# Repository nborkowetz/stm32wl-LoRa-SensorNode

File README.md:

# STM32WL LoRaWAN Prototyping Platform
## Modular Sensor Node for Industrial IoT & Water Quality Monitoring

## 📌 Project Overview
This repository contains the hardware design for a high-performance, ultra-low-power LoRaWAN node based on the **STM32WL55CCU6** SoC. 

This platform serves as an **architectural evaluation board**. It is designed to validate power management strategies, RF performance, and modular sensor interfacing before final product miniaturization.

## 🛠 Technical Specifications

### Core System
* **MCU:** STM32WL55CCU6 (Dual-core ARM Cortex-M4/M0+).
* **Connectivity:** Sub-GHz radio supporting LoRa, (G)FSK, (G)MSK, and BPSK.
* **RF Path:** Optimized 868MHz output with an integrated **BGS12WN6** RF switch and pi-filter matching network.

### Power Management (Ultra-Low Power Focus)
The hardware implements a sophisticated power tree for extreme battery longevity:
* **TPS63900 Buck-Boost:** High-efficiency converter with ultra-low quiescent current, providing a stable 3.3V output across the entire battery discharge curve.
* **LiFePO4 Charging:** Integrated **BQ25071** linear charger, specifically optimized for the safety and cycle-life requirements of LiFePO4 chemistry.
* **Power Gating:** Dedicated load switches to fully disconnect sensor peripherals during deep-sleep cycles, minimizing leakage current.

### PCB Design & Signal Integrity
* **Layer Stack:** 4-layer design (Signal-GND-PWR-Signal) utilizing the **JLC04161H** stackup.
* **Impedance Control:** * **50Ω Single-Ended:** Precision routing for the RF signal path to the antenna.
  * **90Ω Differential:** Calculated for USB data integrity.
* **Manufacturing Ready:** The layout has successfully passed **DFM (Design for Manufacturing)** suites for industrial production standards.

## 🧪 Modular Sensing Interface
To act as a versatile testbed, the board includes:
* Multi-protocol headers (I2C, SPI, UART).
* Analog conditioning circuitry for environmental probes.
* ESD protection on all external sensor interface lines.

## 📂 Project Status
* **Hardware:** Design finalized and DFM-validated. Ready for prototyping.
* **Firmware:** Under active development. Implementing low-power routines and LoRaWAN stack integration using STM32CubeWL HAL.

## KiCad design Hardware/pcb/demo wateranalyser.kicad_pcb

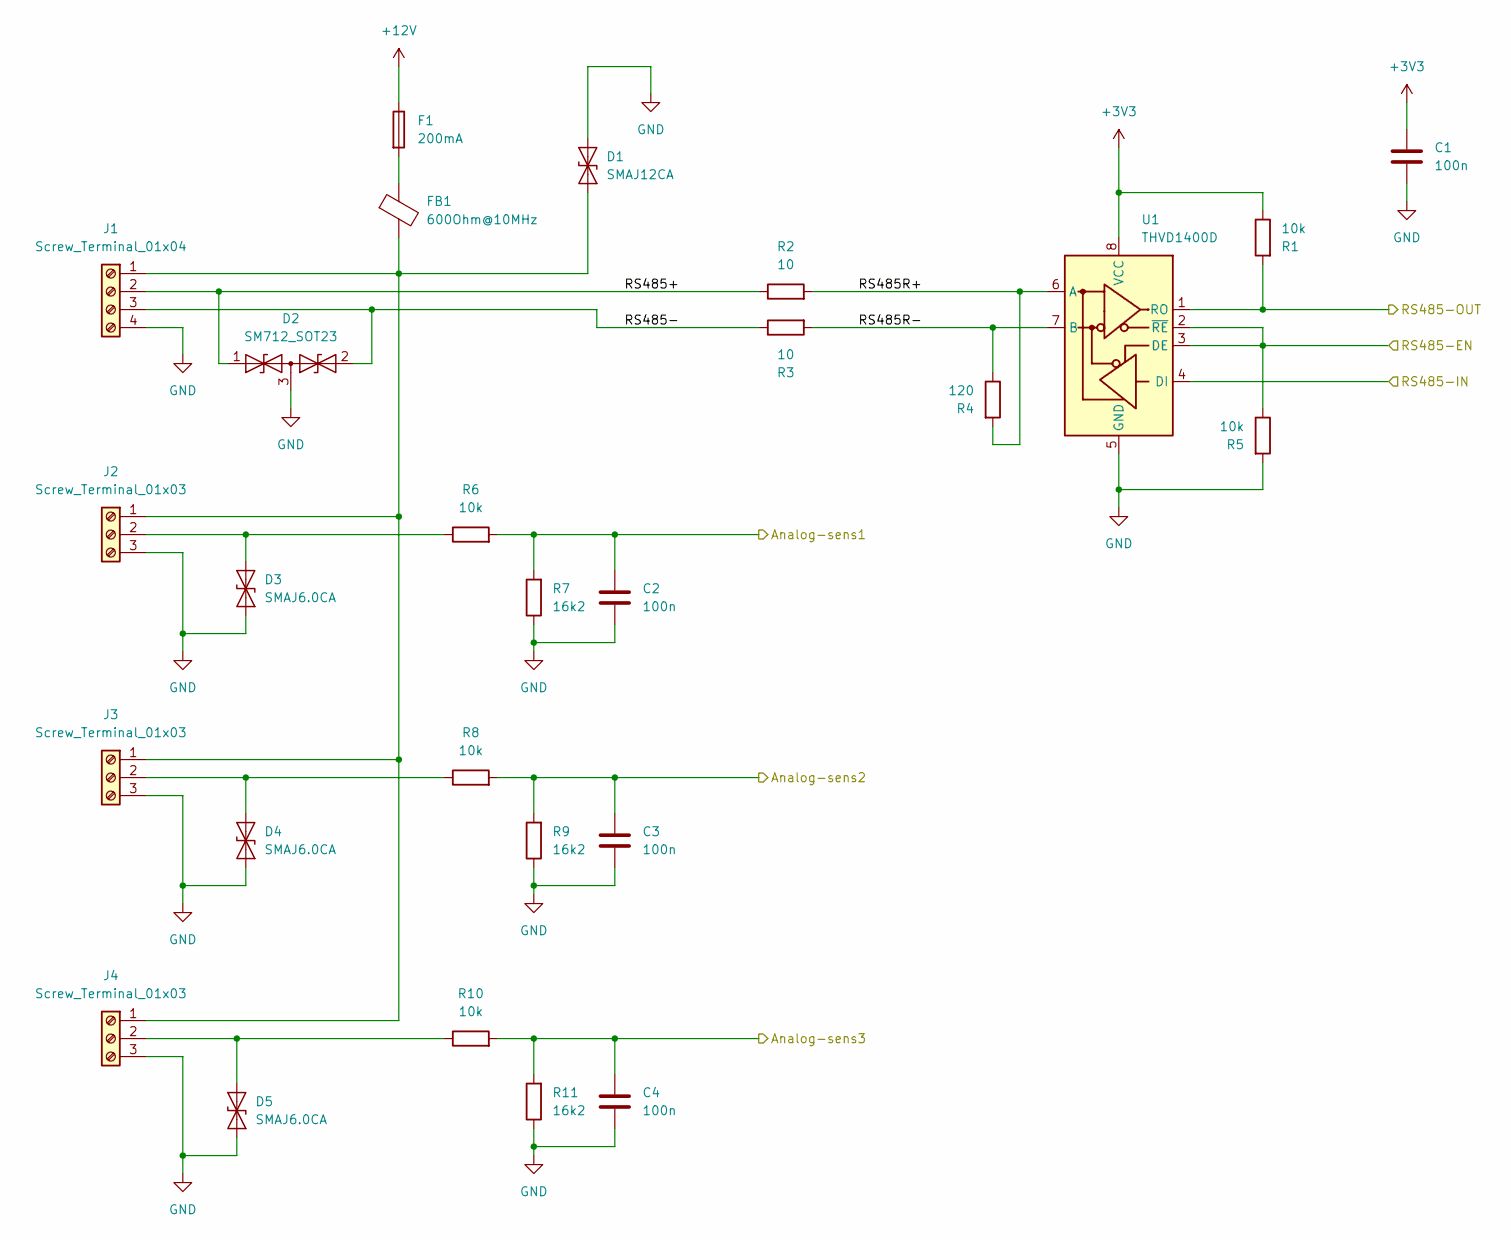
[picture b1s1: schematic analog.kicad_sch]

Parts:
C1, C2, C3, C4: 100n; C_0603_1608Metric
D1: SMAJ12CA; D_SMA
D2: SM712_SOT23; SOT-23
D3, D4, D5: SMAJ6.0CA; D_SMA
F1: 200mA; Fuse_0805_2012Metric
FB1: 600Ohm@10MHz; L_0603_1608Metric
J1: Screw_Terminal_01x04; TerminalBlock_Phoenix_MKDS-1,5-4-5.08_1x04_P5.08mm_Horizont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
J2, J3, J4: Screw_Terminal_01x03; TerminalBlock_Phoenix_MKDS-1,5-3-5.08_1x03_P5.08mm_Horizont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
R1, R5, R6, R8, R10: 10k; R_0603_1608Metric
R2, R3: 10; R_0603_1608Metric
R4: 120; R_0603_1608Metric
R7, R9, R11: 16k2; R_0603_1608Metric
U1: THVD1400D; SOIC-8_3.9x4.9mm_P1.27mm

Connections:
+3V3: C1.1, R1.1, U1.8 (VCC); also elsewhere on the board
+12V: F1.1; also elsewhere on the board
/MCU/ADC-CH2: C2.1, R6.2, R7.2; also elsewhere on the board
/MCU/ADC-CH3: C3.1, R8.2, R9.2; also elsewhere on the board
/MCU/ADC-CH4: C4.1, R10.2, R11.2; also elsewhere on the board
/MCU/RS485-EN: R5.1, U1.2 (~RE), U1.3 (DE); also elsewhere on the board
/MCU/UART-RX: R1.2, U1.1 (RO); also elsewhere on the board
/MCU/UART-TX: U1.4 (DI); also elsewhere on the board
/analog/RS485+: D2.1 (A1), J1.2, R2.1
/analog/RS485-: D2.2 (A2), J1.3, R3.1
/analog/RS485R+: R2.2, R4.2, U1.6 (A)
/analog/RS485R-: R3.2, R4.1, U1.7 (B)
unnamed: D1.1 (A1), FB1.2, J1.1, J2.1, J3.1, J4.1
unnamed: D3.2 (A2), J2.2, R6.1
unnamed: D4.2 (A2), J3.2, R8.1
unnamed: D5.2 (A2), J4.2, R10.1
unnamed: F1.2, FB1.1

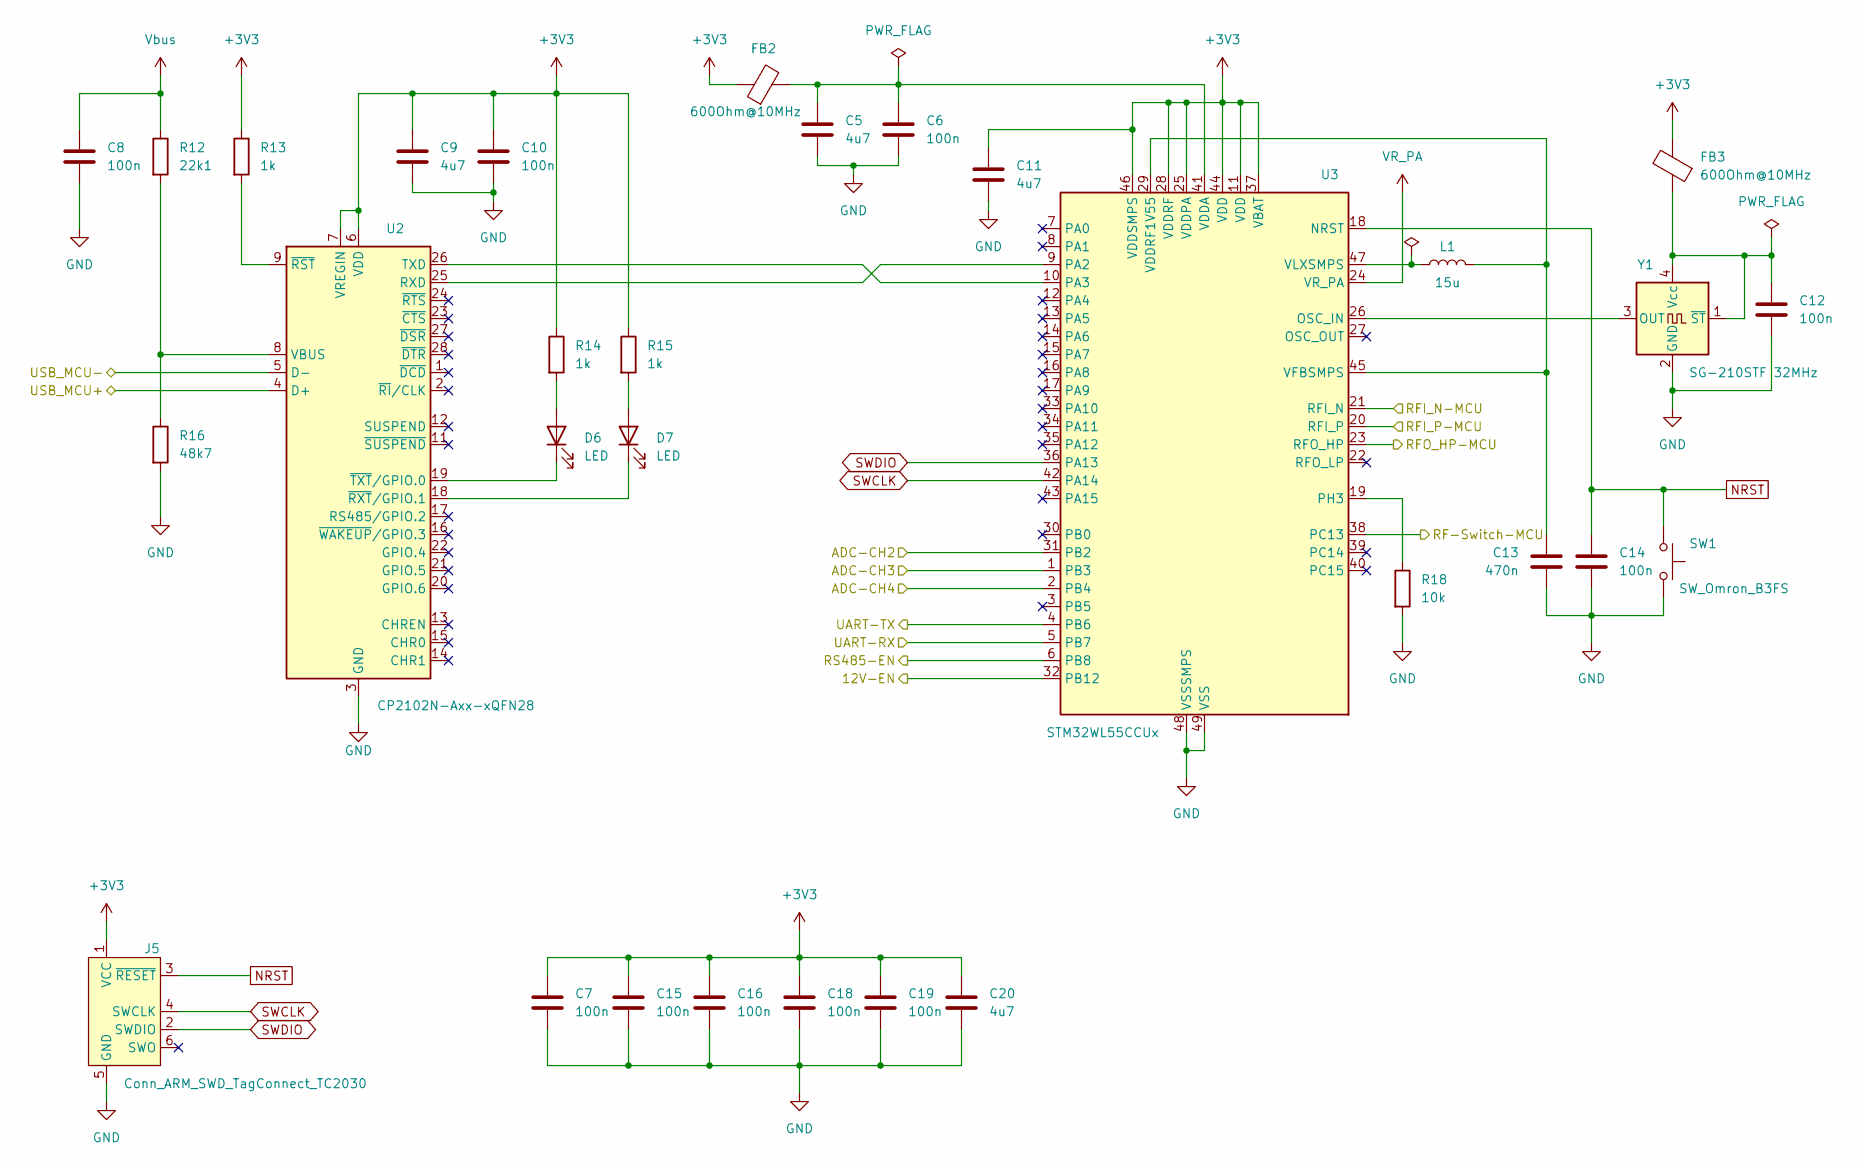
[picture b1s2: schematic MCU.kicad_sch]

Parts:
C5, C9, C11, C20: 4u7; C_0603_1608Metric
C6, C7, C8, C10, C12, C14, C15, C16, C18, C19: 100n; C_0603_1608Metric
C13: 470n; C_0603_1608Metric
D6, D7: LED; LED_0603_1608Metric
FB2, FB3: 600Ohm@10MHz; L_0603_1608Metric
J5: Conn_ARM_SWD_TagConnect_TC2030; Tag-Connect_TC2030-IDC-NL_2x03_P1.27mm_Vertical
L1: 15u; L_0805_2012Metric
R12: 22k1; R_0603_1608Metric
R13, R14, R15: 1k; R_0603_1608Metric
R16: 48k7; R_0603_1608Metric
R18: 10k; R_0603_1608Metric
SW1: SW_Omron_B3FS; SW_SPST_Omron_B3FS-100xP
U2: CP2102N-Axx-xQFN28; QFN-28-1EP_5x5mm_P0.5mm_EP3.35x3.35mm
U3: STM32WL55CCUx; QFN-48-1EP_7x7mm_P0.5mm_EP5.6x5.6mm
Y1: SG-210STF 32MHz; Oscillator_SMD_SeikoEpson_SG210-4Pin_2.5x2.0mm

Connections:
+3V3: C7.1, C9.1, C10.1, C11.1, C15.1, C16.1, C18.1, C19.1, C20.1, FB2.1, FB3.2, J5.1 (VCC), R13.1, R14.1, R15.1, U2.6 (VDD), U2.7 (VREGIN), U3.11 (VDD), U3.25 (VDDPA), U3.28 (VDDRF), U3.37 (VBAT), U3.44 (VDD), U3.46 (VDDSMPS); also elsewhere on the board
/LoRa RF/RF-Switch: U3.38 (PC13); also elsewhere on the board
/LoRa RF/RFI_N: U3.21 (RFI_N); also elsewhere on the board
/LoRa RF/RFI_P: U3.20 (RFI_P); also elsewhere on the board
/LoRa RF/RFO_HP: U3.23 (RFO_HP); also elsewhere on the board
/MCU/12V-EN: U3.32 (PB12); also elsewhere on the board
/MCU/ADC-CH2: U3.31 (PB2); also elsewhere on the board
/MCU/ADC-CH3: U3.1 (PB3); also elsewhere on the board
/MCU/ADC-CH4: U3.2 (PB4); also elsewhere on the board
/MCU/RS485-EN: U3.6 (PB8); also elsewhere on the board
/MCU/UART-RX: U3.5 (PB7); also elsewhere on the board
/MCU/UART-TX: U3.4 (PB6); also elsewhere on the board
/MCU/USB_MCU+: U2.4 (D+); also elsewhere on the board
/MCU/USB_MCU-: U2.5 (D-); also elsewhere on the board
NRST: C14.1, J5.3 (~RESET), SW1.2, U3.18 (NRST)
unnamed: D6.2 (A), R14.2
unnamed: D6.1 (K), U2.19 (~TXT/GPIO.0)
unnamed: D7.2 (A), R15.2
unnamed: D7.1 (K), U2.18 (~RXT/GPIO.1)
unnamed: U2.25 (RXD), U3.9 (PA2)
unnamed: U2.26 (TXD), U3.10 (PA3)
unnamed: R12.2, R16.1, U2.8 (VBUS)
unnamed: R13.2, U2.9 (~RST)
unnamed: U3.26 (OSC_IN), Y1.3 (OUT)
unnamed: R18.1, U3.19 (PH3)
unnamed: C5.1, C6.1, FB2.2, U3.41 (VDDA)
unnamed: C13.1, L1.2, U3.29 (VDDRF1V55), U3.45 (VFBSMPS)
unnamed: L1.1, U3.47 (VLXSMPS)
unnamed: C12.1, FB3.1, Y1.1 (~ST), Y1.4 (Vcc)
SWCLK: J5.4 (SWCLK), U3.42 (PA14)
SWDIO: J5.2 (SWDIO), U3.36 (PA13)
VR_PA: U3.24 (VR_PA); also elsewhere on the board
Vbus: C8.1, R12.1; also elsewhere on the board

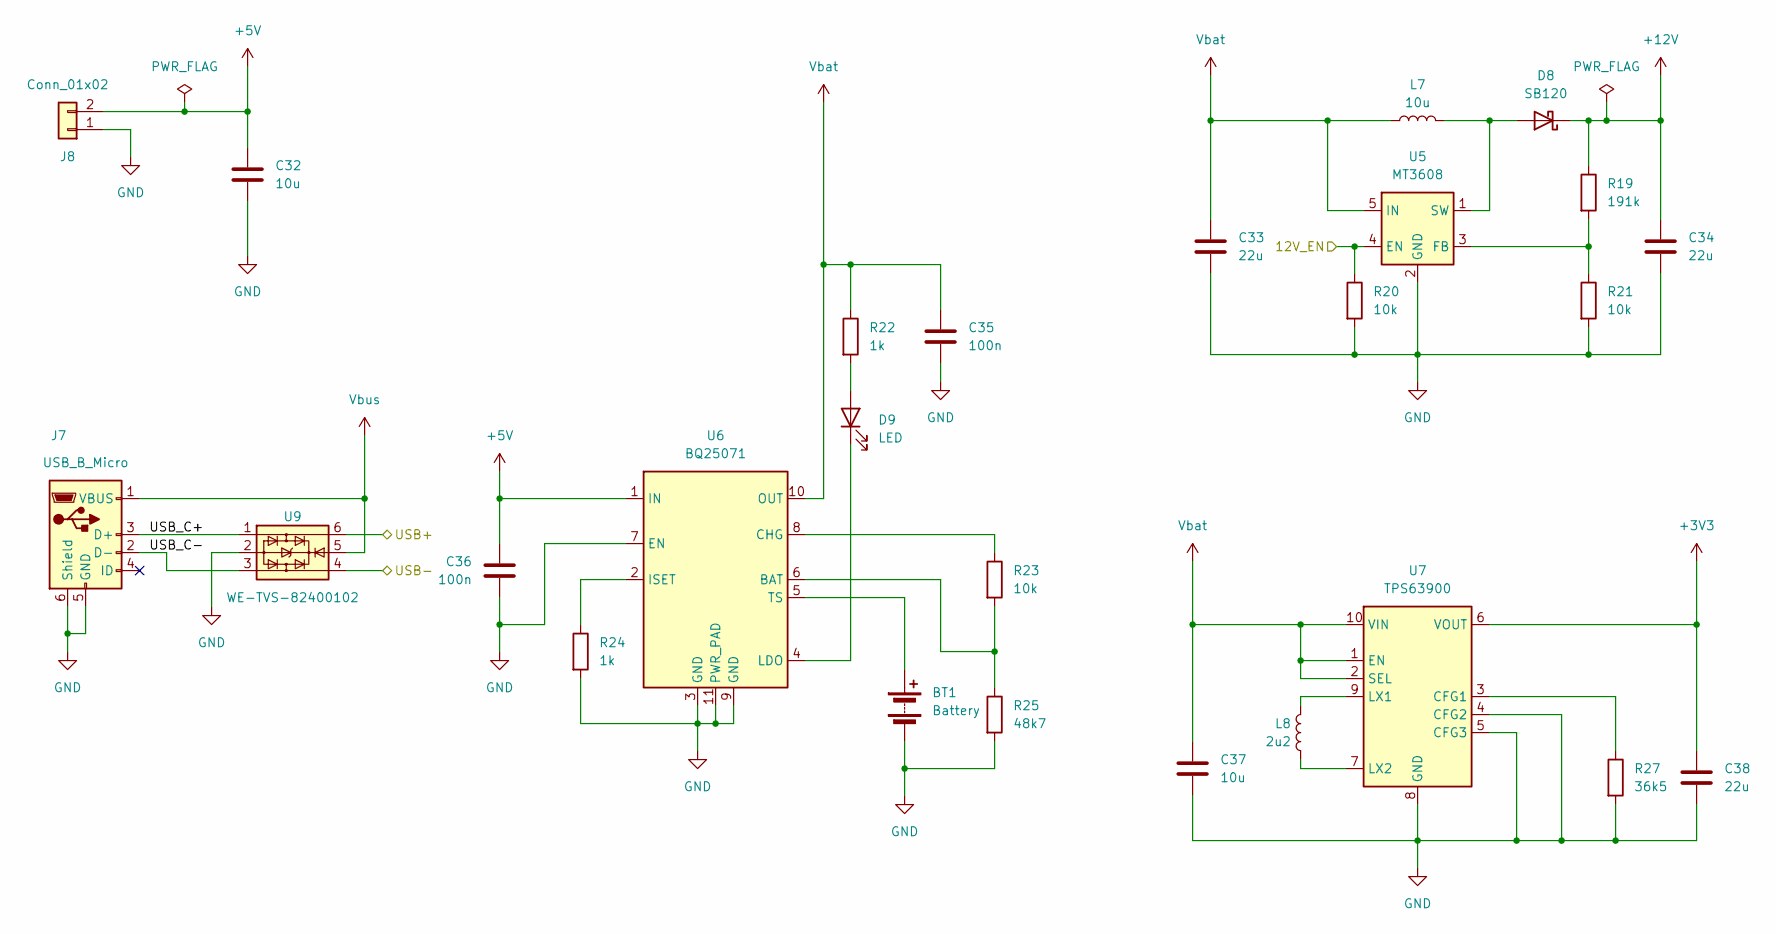
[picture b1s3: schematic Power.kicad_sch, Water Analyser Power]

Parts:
BT1: Battery; PhoenixContact_MCV_1,5_2-G-3.81_1x02_P3.81mm_Vertical
C32, C37: 10u; C_0603_1608Metric
C33, C34, C38: 22u; C_0603_1608Metric
C35, C36: 100n; C_0603_1608Metric
D8: SB120; D_SOD-128
D9: LED; LED_0603_1608Metric
J7: USB_B_Micro; USB_Micro-AB_Molex_47590-0001
J8: Conn_01x02; TerminalBlock_TE_282834-2_1x02_P2.54mm_Horizontal
L7: 10u; L_0805_2012Metric
L8: 2u2; L_0805_2012Metric
R19: 191k; R_0603_1608Metric
R20, R21, R23: 10k; R_0603_1608Metric
R22, R24: 1k; R_0603_1608Metric
R25: 48k7; R_0603_1608Metric
R27: 36k5; R_0603_1608Metric
U5: MT3608; SOT-23-6
U6: BQ25071; WSON-10-1EP_2x3mm_P0.5mm_EP0.84x2.4mm_ThermalVias
U7: TPS63900; WSON-10-1EP_2.5x2.5mm_P0.5mm_EP1.2x2mm_ThermalVias
U9: WE-TVS-82400102; SOT-23-6_Handsoldering

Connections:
+3V3: C38.1, U7.6 (VOUT); also elsewhere on the board
+5V: C32.1, C36.1, J8.2, U6.1 (IN)
+12V: C34.1, D8.1 (K), R19.1; also elsewhere on the board
/MCU/12V-EN: R20.1, U5.4 (EN); also elsewhere on the board
/MCU/USB_MCU+: U9.6; also elsewhere on the board
/MCU/USB_MCU-: U9.4; also elsewhere on the board
/Power/USB_C+: J7.3 (D+), U9.1
/Power/USB_C-: J7.2 (D-), U9.3
unnamed: BT1.1 (+), U6.5 (TS)
unnamed: D8.2 (A), L7.2, U5.1 (SW)
unnamed: D9.2 (A), R22.2
unnamed: D9.1 (K), U6.4 (LDO)
unnamed: R19.2, R21.1, U5.3 (FB)
unnamed: R23.2, R25.1, U6.6 (BAT)
unnamed: R23.1, U6.8 (CHG)
unnamed: R24.1, U6.2 (ISET)
unnamed: R27.1, U7.3 (CFG1)
unnamed: L8.1, U7.9 (LX1)
unnamed: L8.2, U7.7 (LX2)
Vbat: C33.1, C35.1, C37.1, L7.1, R22.1, U5.5 (IN), U6.10 (OUT), U7.1 (EN), U7.2 (SEL), U7.10 (VIN)
Vbus: J7.1 (VBUS), U9.5; also elsewhere on the board

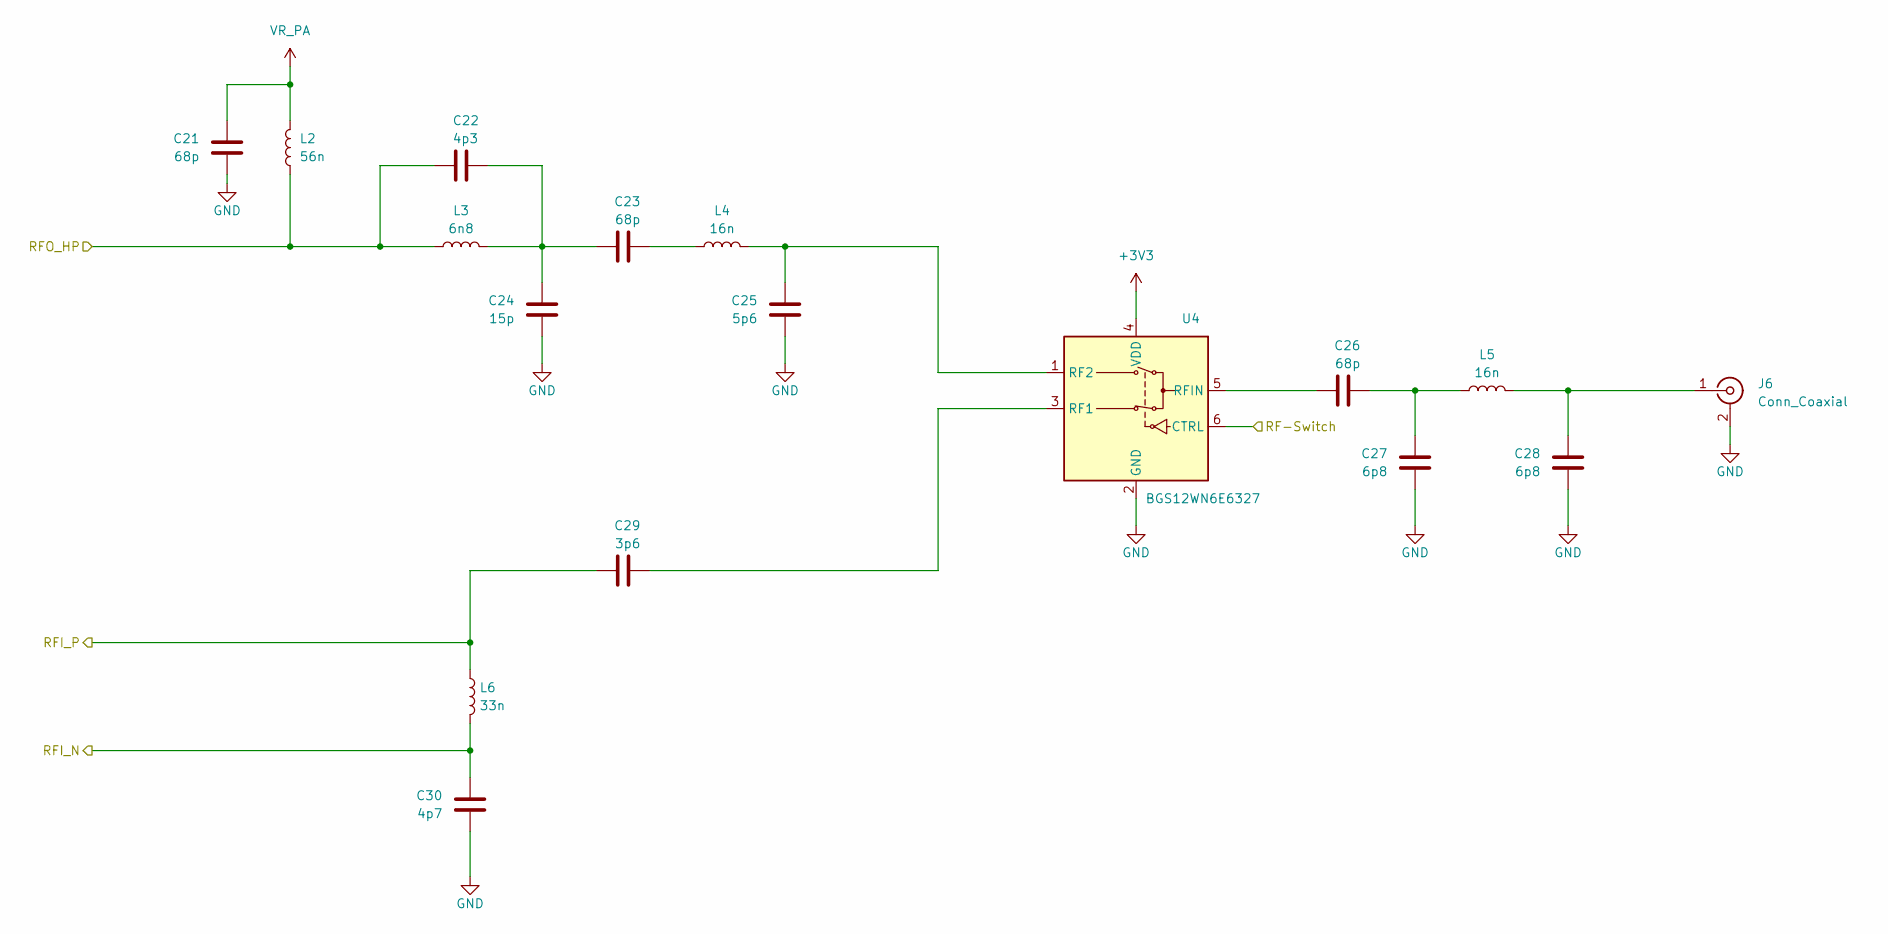
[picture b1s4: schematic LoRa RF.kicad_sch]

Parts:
C21, C23, C26: 68p; C_0603_1608Metric
C22: 4p3; C_0603_1608Metric
C24: 15p; C_0603_1608Metric
C25: 5p6; C_0603_1608Metric
C27, C28: 6p8; C_0603_1608Metric
C29: 3p6; C_0603_1608Metric
C30: 4p7; C_0603_1608Metric
J6: Conn_Coaxial; BNC_TEConnectivity_1478035_Horizontal
L2: 56n; L_0603_1608Metric
L3: 6n8; L_0603_1608Metric
L4, L5: 16n; L_0603_1608Metric
L6: 33n; L_0603_1608Metric
U4: BGS12WN6E6327; Infineon_PG-TSNP-6-10_0.7x1.1mm_0.7x1.1mm_P0.4mm

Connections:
+3V3: U4.4 (VDD); also elsewhere on the board
/LoRa RF/RF-Switch: U4.6 (CTRL); also elsewhere on the board
/LoRa RF/RFI_N: C30.1, L6.2; also elsewhere on the board
/LoRa RF/RFI_P: C29.1, L6.1; also elsewhere on the board
/LoRa RF/RFO_HP: C22.2, L2.1, L3.1; also elsewhere on the board
unnamed: C22.1, C23.1, C24.1, L3.2
unnamed: C23.2, L4.1
unnamed: C26.2, C27.1, L5.1
unnamed: C28.1, J6.1 (In), L5.2
unnamed: C29.2, U4.3 (RF1)
unnamed: C25.1, L4.2, U4.1 (RF2)
unnamed: C26.1, U4.5 (RFIN)
VR_PA: C21.1, L2.2; also elsewhere on the board

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
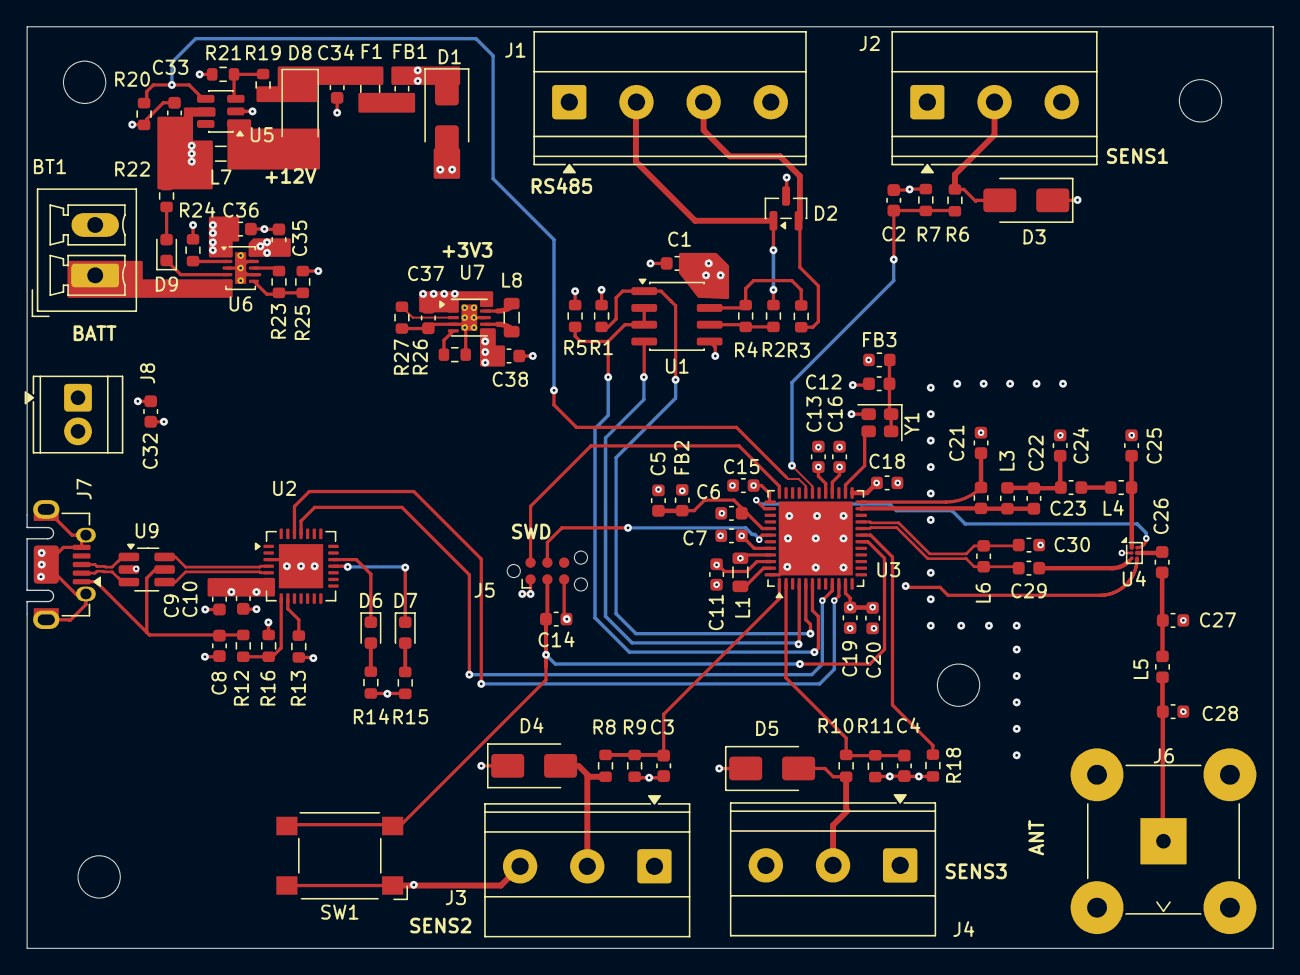
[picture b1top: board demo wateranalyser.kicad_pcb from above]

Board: 4 copper layers, 94.2 x 69.7 mm, 102 parts (0 on the bottom side), 67 nets.

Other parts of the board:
R26: 16k2; R_0603_1608Metric

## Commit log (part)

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2026-01-08 changed gitignore setup
2026-01-08 Create README.md
    added readme
